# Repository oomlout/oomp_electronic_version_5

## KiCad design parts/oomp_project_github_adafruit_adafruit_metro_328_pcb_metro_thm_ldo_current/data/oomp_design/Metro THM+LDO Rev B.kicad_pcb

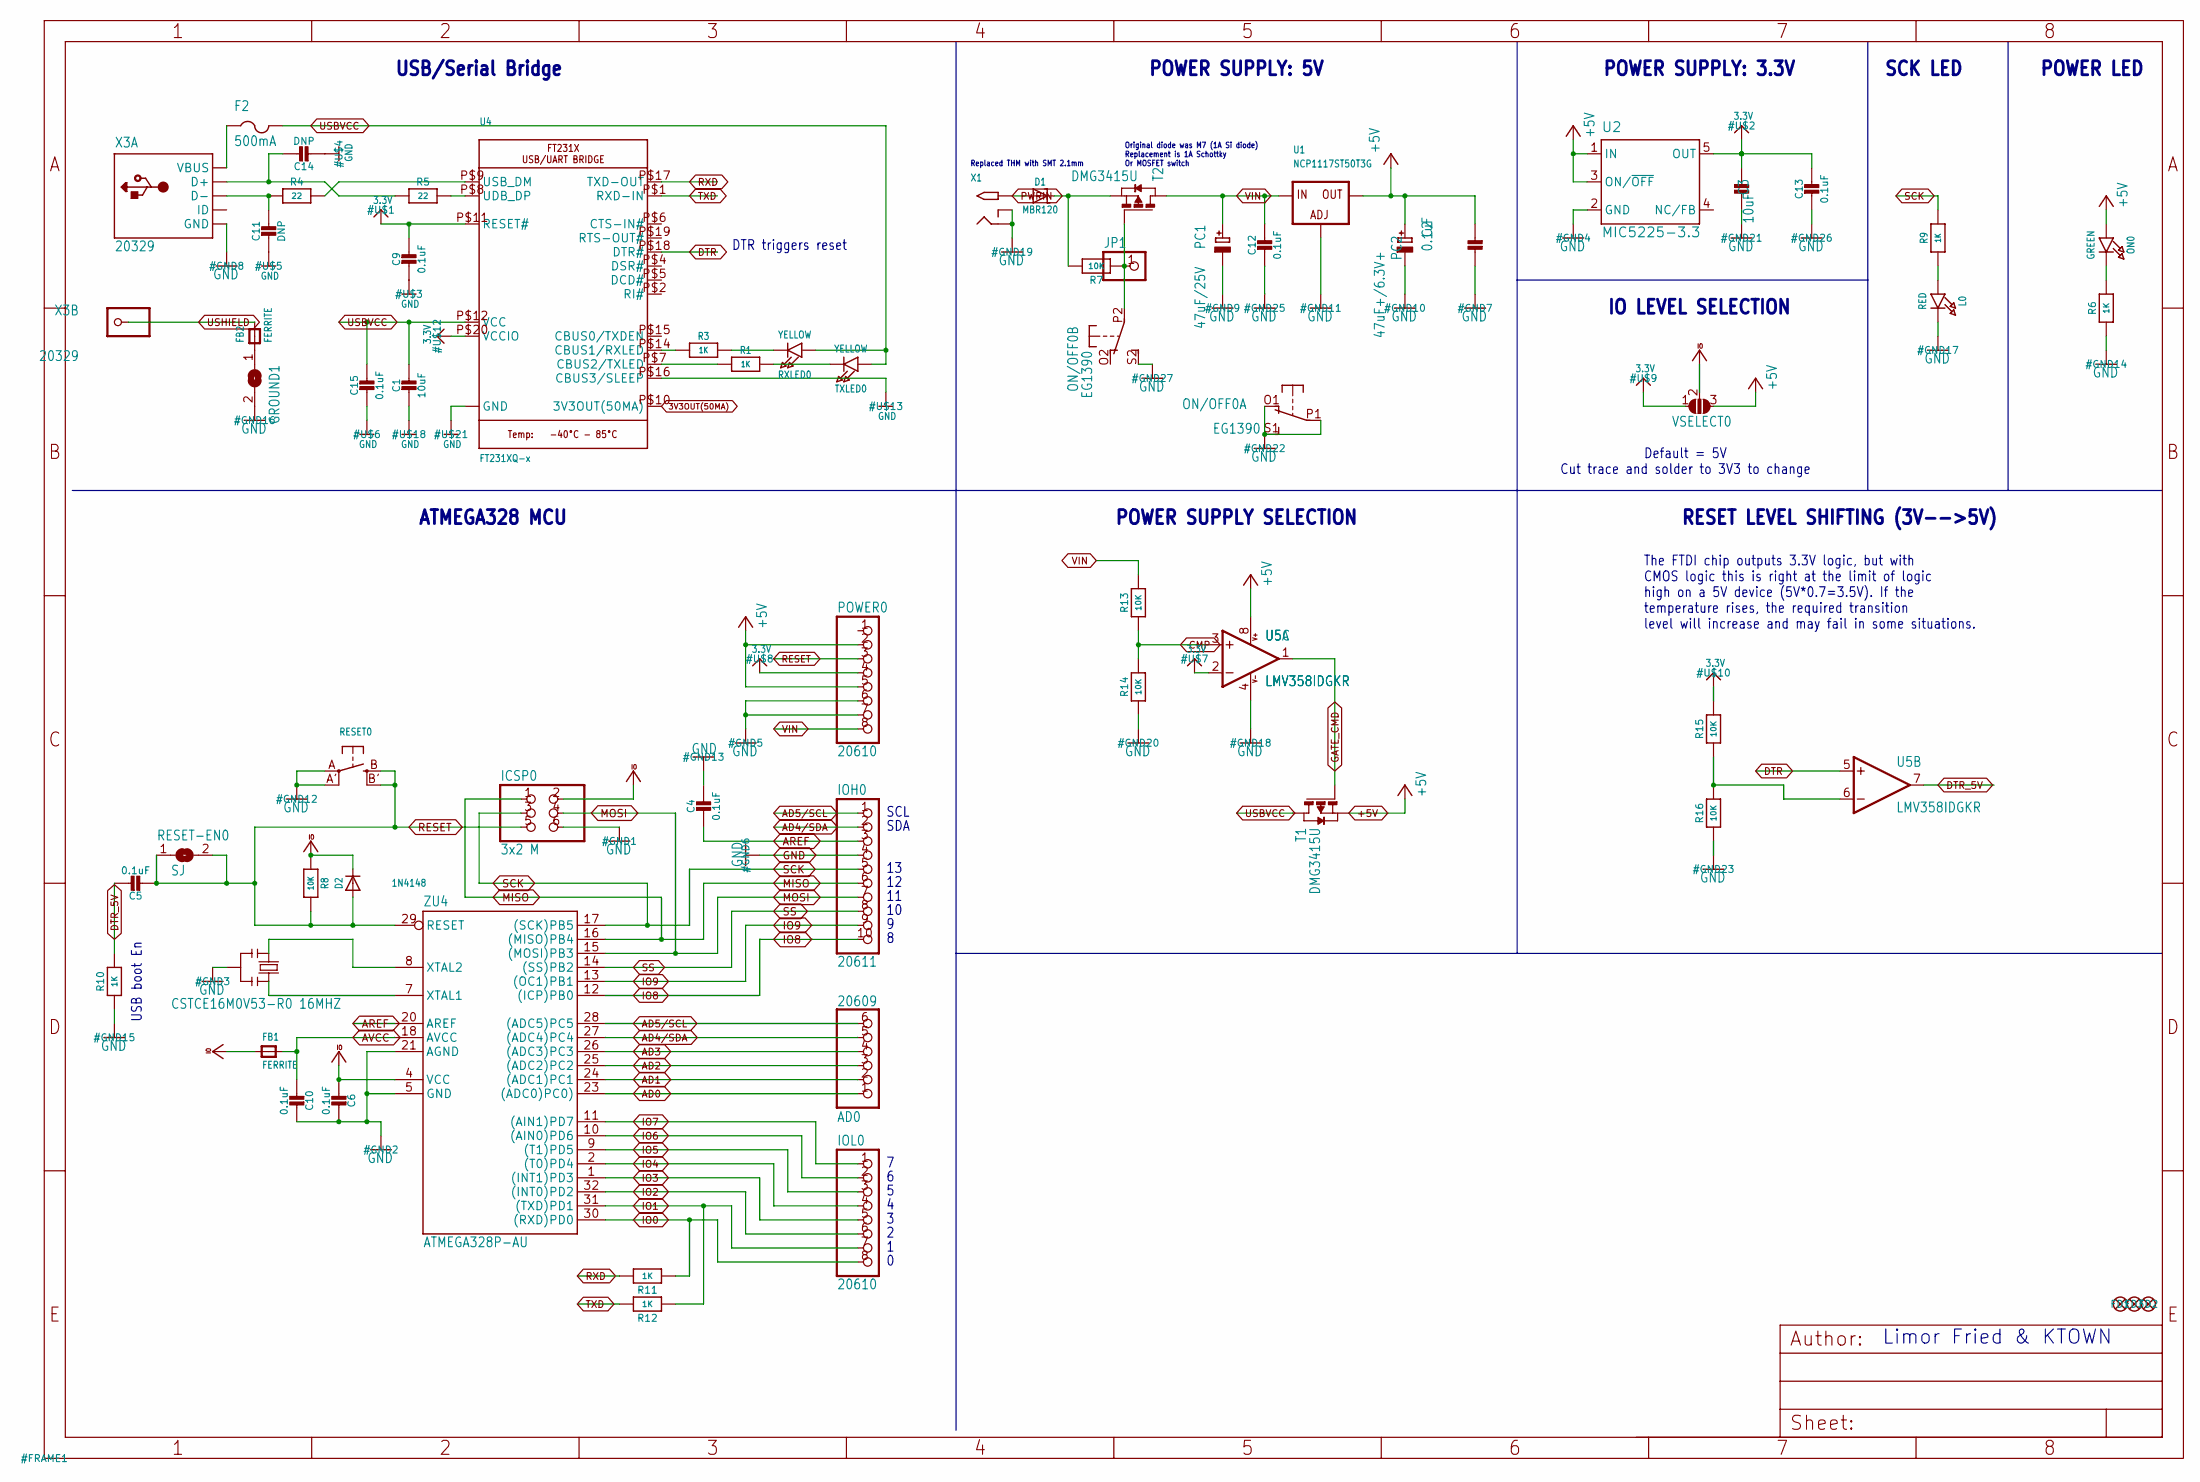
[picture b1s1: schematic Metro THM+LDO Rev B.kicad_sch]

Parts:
AD0: 20609; 1X06_OVAL
C1, C3: 10uF; 0805-NO
C2, C4, C5, C6, C9, C12, C13, C15: 0.1uF; 0805-NO
C10: 0.1uF; 0805_10MGAP
C11, C14: DNP; 0805-NO
D1: MBR120; SOD-123
D2: 1N4148; SOD-323
F2: 500mA; R1206
FB1, FB2: FERRITE; 0805-NO
FD1, FD2, FD3: FIDUCIAL""; FIDUCIAL_1MM
GROUND1: SJ
ICSP0: 3x2 M; 2X03_ROUND_70MIL
IOH0: 20611; 1X10_OVAL
IOL0: 20610; 1X08_OVAL
JP1: HEADER-1X1ROUND; 1X01_ROUND
L0: RED; CHIPLED_0805_NOOUTLINE
ON0: GREEN; CHIPLED_0805_NOOUTLINE
ON/OFF0: EG1390
PC1: 47uF/25V; PANASONIC_D
PC2: 47uF+/6.3V+; PANASONIC_D
POWER0: 20610; 1X08_OVAL
R1, R3, R6, R9, R10, R11, R12: 1K; 0805-NO
R4, R5: 22; 0805-NO
R7, R13, R14, R15, R16: 10K; 0805-NO
R8: 10K; _0805MP
RESET0: SWITCH_TACT_SMT; EVQ-Q2
RESET-EN0: SJ
RXLED0: YELLOW; CHIPLED_0805_NOOUTLINE
T1, T2: DMG3415U; SOT-23
TXLED0: YELLOW; CHIPLED_0805_NOOUTLINE
U1: NCP1117ST50T3G; SOT223-R
U2: MIC5225-3.3; SOT23-DBV
U4: FT231XQ-x; QFN20_4MM
U5: LMV358IDGKR; MSOP08
VSELECT0: SOLDERJUMPER_2WAY; SOLDERJUMPER_2WAY_OPEN_NOPASTE
X1: 2.1MMJACKSMT; DCJACK_2MM_SMT
X3: 20329; 4UCONN_20329
Y2: CSTCE16M0V53-R0 16MHZ; RESONATOR
ZU4: ATMEGA328P-AU; TQFP32-08

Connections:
3.3V: C3.2, C9.1, C13.1, POWER0.4, R15.2, U2.5 (OUT), U4.P$11 (RESET#), U4.P$20 (VCCIO), U5.2 (-IN), VSELECT0.1
3V3OUT(50MA): U4.P$10 (3V3OUT(50MA))
+5V: C2.2, ON0.A, PC2.+, POWER0.2, POWER0.5, T1.2 (S), U1.2 (OUT), U1.4 (OUT), U2.1 (IN), U2.3 (ON/~OFF), U5.8 (V+), VSELECT0.3
AD0: AD0.1, ZU4.23 ((ADC0)PC0))
AD1: AD0.2, ZU4.24 ((ADC1)PC1)
AD2: AD0.3, ZU4.25 ((ADC2)PC2)
AD3: AD0.4, ZU4.26 ((ADC3)PC3)
AD4/SDA: AD0.5, IOH0.2, ZU4.27 ((ADC4)PC4)
AD5/SCL: AD0.6, IOH0.1, ZU4.28 ((ADC5)PC5)
AREF: C4.2, IOH0.3, ZU4.20 (AREF)
AVCC: C10.2, FB1.2, ZU4.18 (AVCC)
CMP: R13.1, R14.2, U5.3 (+IN)
D+: C14.1, R5.1, X3.D+
D-: C11.1, R4.1, X3.D-
DTR: U4.P$18 (DTR#), U5.5 (+IN)
DTR_5V: C5.1, R10.2, U5.7 (OUT)
GATE_CMD: T1.3 (G), U5.1 (OUT)
GND: C1.2, C2.1, C3.1, C4.1, C6.1, C9.2, C10.1, C11.2, C12.2, C13.2, C14.2, C15.2, GROUND1.2, ICSP0.6, IOH0.4, L0.C, ON/OFF0.O1 (O), ON/OFF0.P1, ON/OFF0.S1 (S), ON/OFF0.S2 (S), PC1.-, PC2.-, POWER0.6, POWER0.7, R6.1, R10.1, R14.1, R16.1, RESET0.A, RESET0.A' (P1), U1.1 (ADJ), U2.2 (GND), U4.P$3 (GND), U4.P$13 (GND), U4.P$16 (CBUS3/SLEEP), U4.P$21 (GND), U5.4 (V-), X1.GND (RING), X1.GNDBREAK (RING_SW), X3.GND, Y2.2, ZU4.5 (GND), ZU4.21 (AGND)
IO0: IOL0.8, R11.1, ZU4.30 ((RXD)PD0)
IO1: IOL0.7, R12.1, ZU4.31 ((TXD)PD1)
IO2: IOL0.6, ZU4.32 ((INT0)PD2)
IO3: IOL0.5, ZU4.1 ((INT1)PD3)
IO4: IOL0.4, ZU4.2 ((T0)PD4)
IO5: IOL0.3, ZU4.9 ((T1)PD5)
IO6: IOL0.2, ZU4.10 ((AIN0)PD6)
IO7: IOL0.1, ZU4.11 ((AIN1)PD7)
IO8: IOH0.10, ZU4.12 ((ICP)PB0)
IO9: IOH0.9, ZU4.13 ((OC1)PB1)
MISO: ICSP0.1, IOH0.6, ZU4.16 ((MISO)PB4)
MOSI: ICSP0.4, IOH0.7, ZU4.15 ((MOSI)PB3)
unnamed: L0.A, R9.1
unnamed: FB2.1, GROUND1.1
unnamed: ON0.C, R6.2
unnamed: R3.2, U4.P$14 (CBUS1/RXLED)
unnamed: R3.1, RXLED0.C
unnamed: R1.2, U4.P$7 (CBUS2/TXLED)
unnamed: R1.1, TXLED0.C
unnamed: R4.2, U4.P$9 (USB_DM)
unnamed: R5.2, U4.P$8 (UDB_DP)
unnamed: R15.1, R16.2, U5.6 (-IN)
unnamed: JP1.1, ON/OFF0.P2, R7.1, T2.3 (G)
unnamed: D1.C, R7.2, T2.2 (S)
PWRIN: D1.A, X1.PWR2 (TIP)
RESET: C5.2, D2.A, ICSP0.5, POWER0.3, R8.1, RESET0.B (S), RESET0.B' (S1), RESET-EN0.1, RESET-EN0.2, ZU4.29 (RESET)
RXD: R11.2, U4.P$17 (TXD-OUT)
SCK: ICSP0.3, IOH0.5, R9.2, ZU4.17 ((SCK)PB5)
SS: IOH0.8, ZU4.14 ((SS)PB2)
TXD: R12.2, U4.P$1 (RXD-IN)
USBVCC: C1.1, C15.1, F2.2, RXLED0.A, T1.1 (D), TXLED0.A, U4.P$12 (VCC)
USHIELD: FB2.2, X3.BASE@1 (1), X3.BASE@2 (1), X3.SPRT@1 (1), X3.SPRT@2 (1), X3.SPRT@3 (1), X3.SPRT@4 (1)
VBUS: F2.1, X3.VBUS
VCCIO: C6.2, D2.C, FB1.1, ICSP0.2, R8.2, VSELECT0.2, ZU4.4 (VCC)
VIN: C12.1, PC1.+, POWER0.8, R13.2, T2.1 (D), U1.3 (IN)
XTAL1: Y2.3, ZU4.7 (XTAL1)
XTAL2: Y2.1, ZU4.8 (XTAL2)

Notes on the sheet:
Limor Fried & KTOWN
SDA
POWER SUPPLY SELECTION
Original diode was M7 (1A Si diode) Replacement is 1A Schottky Or MOSFET switch
POWER SUPPLY: 3.3V
POWER LED
The FTDI chip outputs 3.3V logic, but with CMOS logic this is right at the limit of logic high on a 5V device (5V*0.7=3.5V). If the temperature rises, the required transition level will increase and may fail in some situations.
Default = 5V Cut trace and solder to 3V3 to change
SCK LED
RESET LEVEL SHIFTING (3V-->5V)
SCL
USB boot En
IO LEVEL SELECTION
DTR triggers reset
USB/Serial Bridge
POWER SUPPLY: 5V
Replaced THM with SMT 2.1mm
ATMEGA328 MCU

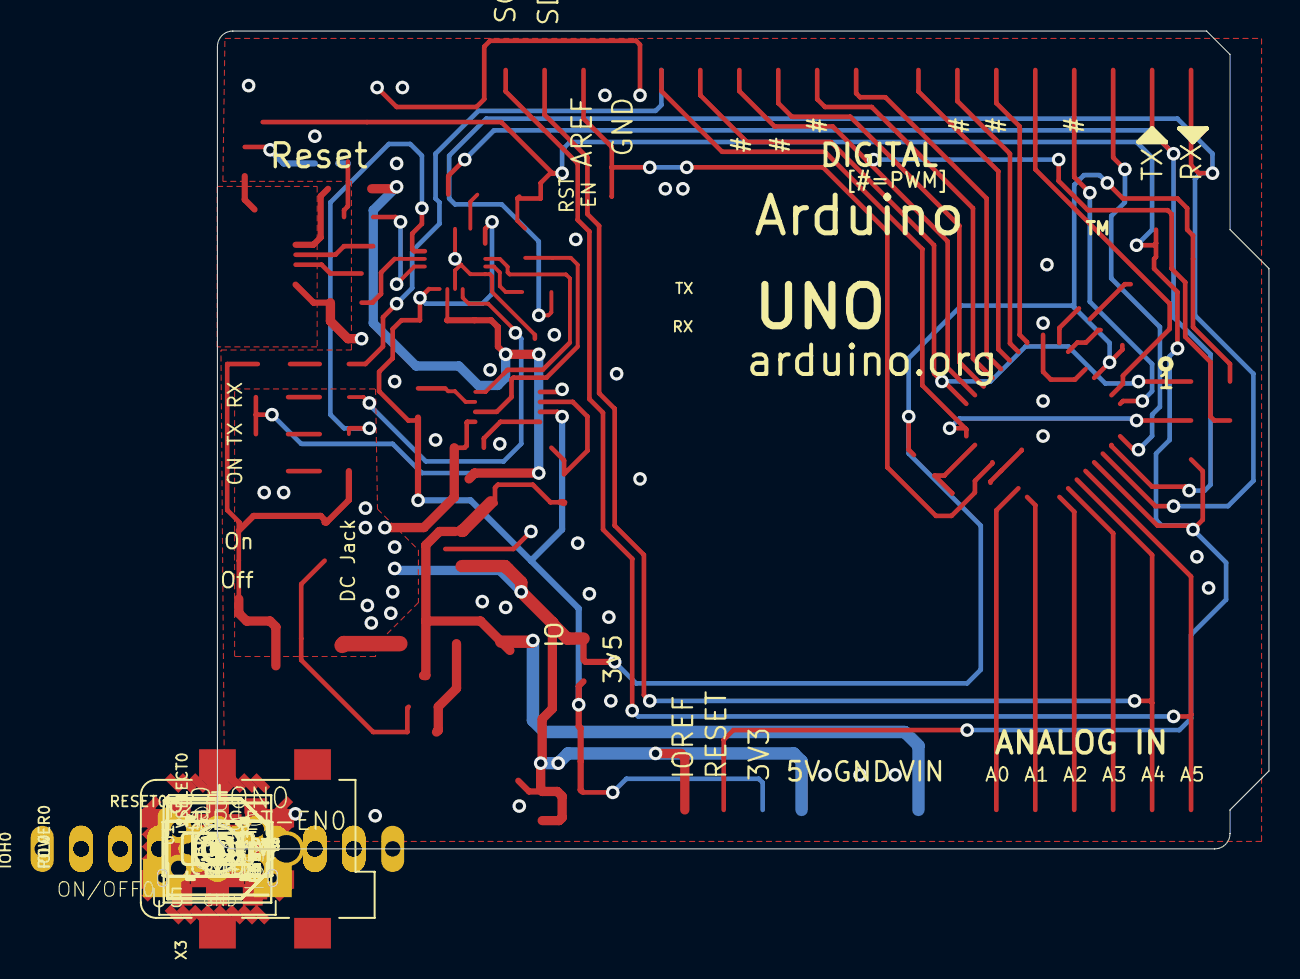
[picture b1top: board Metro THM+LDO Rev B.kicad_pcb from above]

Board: 2 copper layers, 72.5 x 55.8 mm, 70 parts (1 on the bottom side), 54 nets.

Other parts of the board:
U$11: METROSILK_TOP
U$14: METROSILK_BOT
U$15: PCBFEAT-REV-040
UNK_HOLE_0: dummyfp0
UNK_HOLE_1: dummyfp1
UNK_HOLE_2: dummyfp2
UNK_HOLE_3: dummyfp3

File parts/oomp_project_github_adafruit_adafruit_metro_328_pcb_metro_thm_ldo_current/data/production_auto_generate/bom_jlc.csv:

Comment,Designator,Footprint,LCSC Part #
,JP1,Metro THM+LDO Rev B-import-fps:1X01_ROUND,C7501259
,RESET0,Metro THM+LDO Rev B-import-fps:EVQ-Q2,
,U$14,Metro THM+LDO Rev B-import-fps:METROSILK_BOT,
,U$11,Metro THM+LDO Rev B-import-fps:METROSILK_TOP,
,U$15,Metro THM+LDO Rev B-import-fps:PCBFEAT-REV-040,
,"GROUND1,RESET-EN0",Metro THM+LDO Rev B-import-fps:SJ,
,VSELECT0,Metro THM+LDO Rev B-import-fps:SOLDERJUMPER_2WAY_OPEN_NOPASTE,
0.1uF,"C2,C4,C5,C6,C9,C12,C13,C15",Metro THM+LDO Rev B-import-fps:0805-NO,
0.1uF,C10,Metro THM+LDO Rev B-import-fps:0805_10MGAP,
10K,"R7,R13,R14,R15,R16",Metro THM+LDO Rev B-import-fps:0805-NO,C17414
10K,R8,Metro THM+LDO Rev B-import-fps:_0805MP,C17414
10uF,"C1,C3",Metro THM+LDO Rev B-import-fps:0805-NO,
1K,"R1,R3,R6,R9,R10,R11,R12",Metro THM+LDO Rev B-import-fps:0805-NO,C17513
1N4148,D2,Metro THM+LDO Rev B-import-fps:SOD-323,
2.1MMJACKSMT,X1,Metro THM+LDO Rev B-import-fps:DCJACK_2MM_SMT,
20329,X3,Metro THM+LDO Rev B-import-fps:4UCONN_20329,
20609,AD0,Metro THM+LDO Rev B-import-fps:1X06_OVAL,C37208
20610,"IOL0,POWER0",Metro THM+LDO Rev B-import-fps:1X08_OVAL,C492421
20611,IOH0,Metro THM+LDO Rev B-import-fps:1X10_OVAL,C57369
22,"R4,R5",Metro THM+LDO Rev B-import-fps:0805-NO,C2907310
3x2 M,ICSP0,Metro THM+LDO Rev B-import-fps:2X03_ROUND_70MIL,
47uF+/6.3V+,PC2,Metro THM+LDO Rev B-import-fps:PANASONIC_D,
47uF/25V,PC1,Metro THM+LDO Rev B-import-fps:PANASONIC_D,
500mA,F2,Metro THM+LDO Rev B-import-fps:R1206,
ATMEGA328P-AU,ZU4,Metro THM+LDO Rev B-import-fps:TQFP32-08,
CSTCE16M0V53-R0 16MHZ,Y2,Metro THM+LDO Rev B-import-fps:RESONATOR,
DMG3415U,"T1,T2",Metro THM+LDO Rev B-import-fps:SOT-23,
DNP,"C11,C14",Metro THM+LDO Rev B-import-fps:0805-NO,
EG1390,ON/OFF0,Metro THM+LDO Rev B-import-fps:EG1390,
FERRITE,"FB1,FB2",Metro THM+LDO Rev B-import-fps:0805-NO,
"FIDUCIAL""""","FD1,FD2,FD3",Metro THM+LDO Rev B-import-fps:FIDUCIAL_1MM,
FT231XQ-x ,U4,Metro THM+LDO Rev B-import-fps:QFN20_4MM,
GREEN,ON0,Metro THM+LDO Rev B-import-fps:CHIPLED_0805_NOOUTLINE,
LMV358IDGKR,U5,Metro THM+LDO Rev B-import-fps:MSOP08,
MBR120,D1,Metro THM+LDO Rev B-import-fps:SOD-123,
MIC5225-3.3,U2,Metro THM+LDO Rev B-import-fps:SOT23-DBV,
NCP1117ST50T3G,U1,Metro THM+LDO Rev B-import-fps:SOT223-R,
RED,L0,Metro THM+LDO Rev B-import-fps:CHIPLED_0805_NOOUTLINE,
YELLOW,"RXLED0,TXLED0",Metro THM+LDO Rev B-import-fps:CHIPLED_0805_NOOUTLINE,

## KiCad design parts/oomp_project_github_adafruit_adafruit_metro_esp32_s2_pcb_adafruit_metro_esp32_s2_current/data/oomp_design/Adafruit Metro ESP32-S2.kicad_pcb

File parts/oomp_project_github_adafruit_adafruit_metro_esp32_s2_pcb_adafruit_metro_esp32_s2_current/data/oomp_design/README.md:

# OOMP KiCad design copy

Open `Adafruit Metro ESP32-S2.kicad_pro` (or the `.kicad_pcb` / `.kicad_sch`) in KiCad. Local OOMP libraries are under `libraries/`. Original inputs are preserved in [../original/](../original/).

Only verified unchanged installed KiCad defaults were renamed. Modified, custom, unmatched and unavailable items remain unchanged. Soldering variants are never swapped during conversion. Existing pad coordinates, nets and UUIDs are preserved.

See [conversion_report.yaml](conversion_report.yaml) for every conversion and skip. Copy this directory before editing; regeneration refuses to overwrite edited design files.

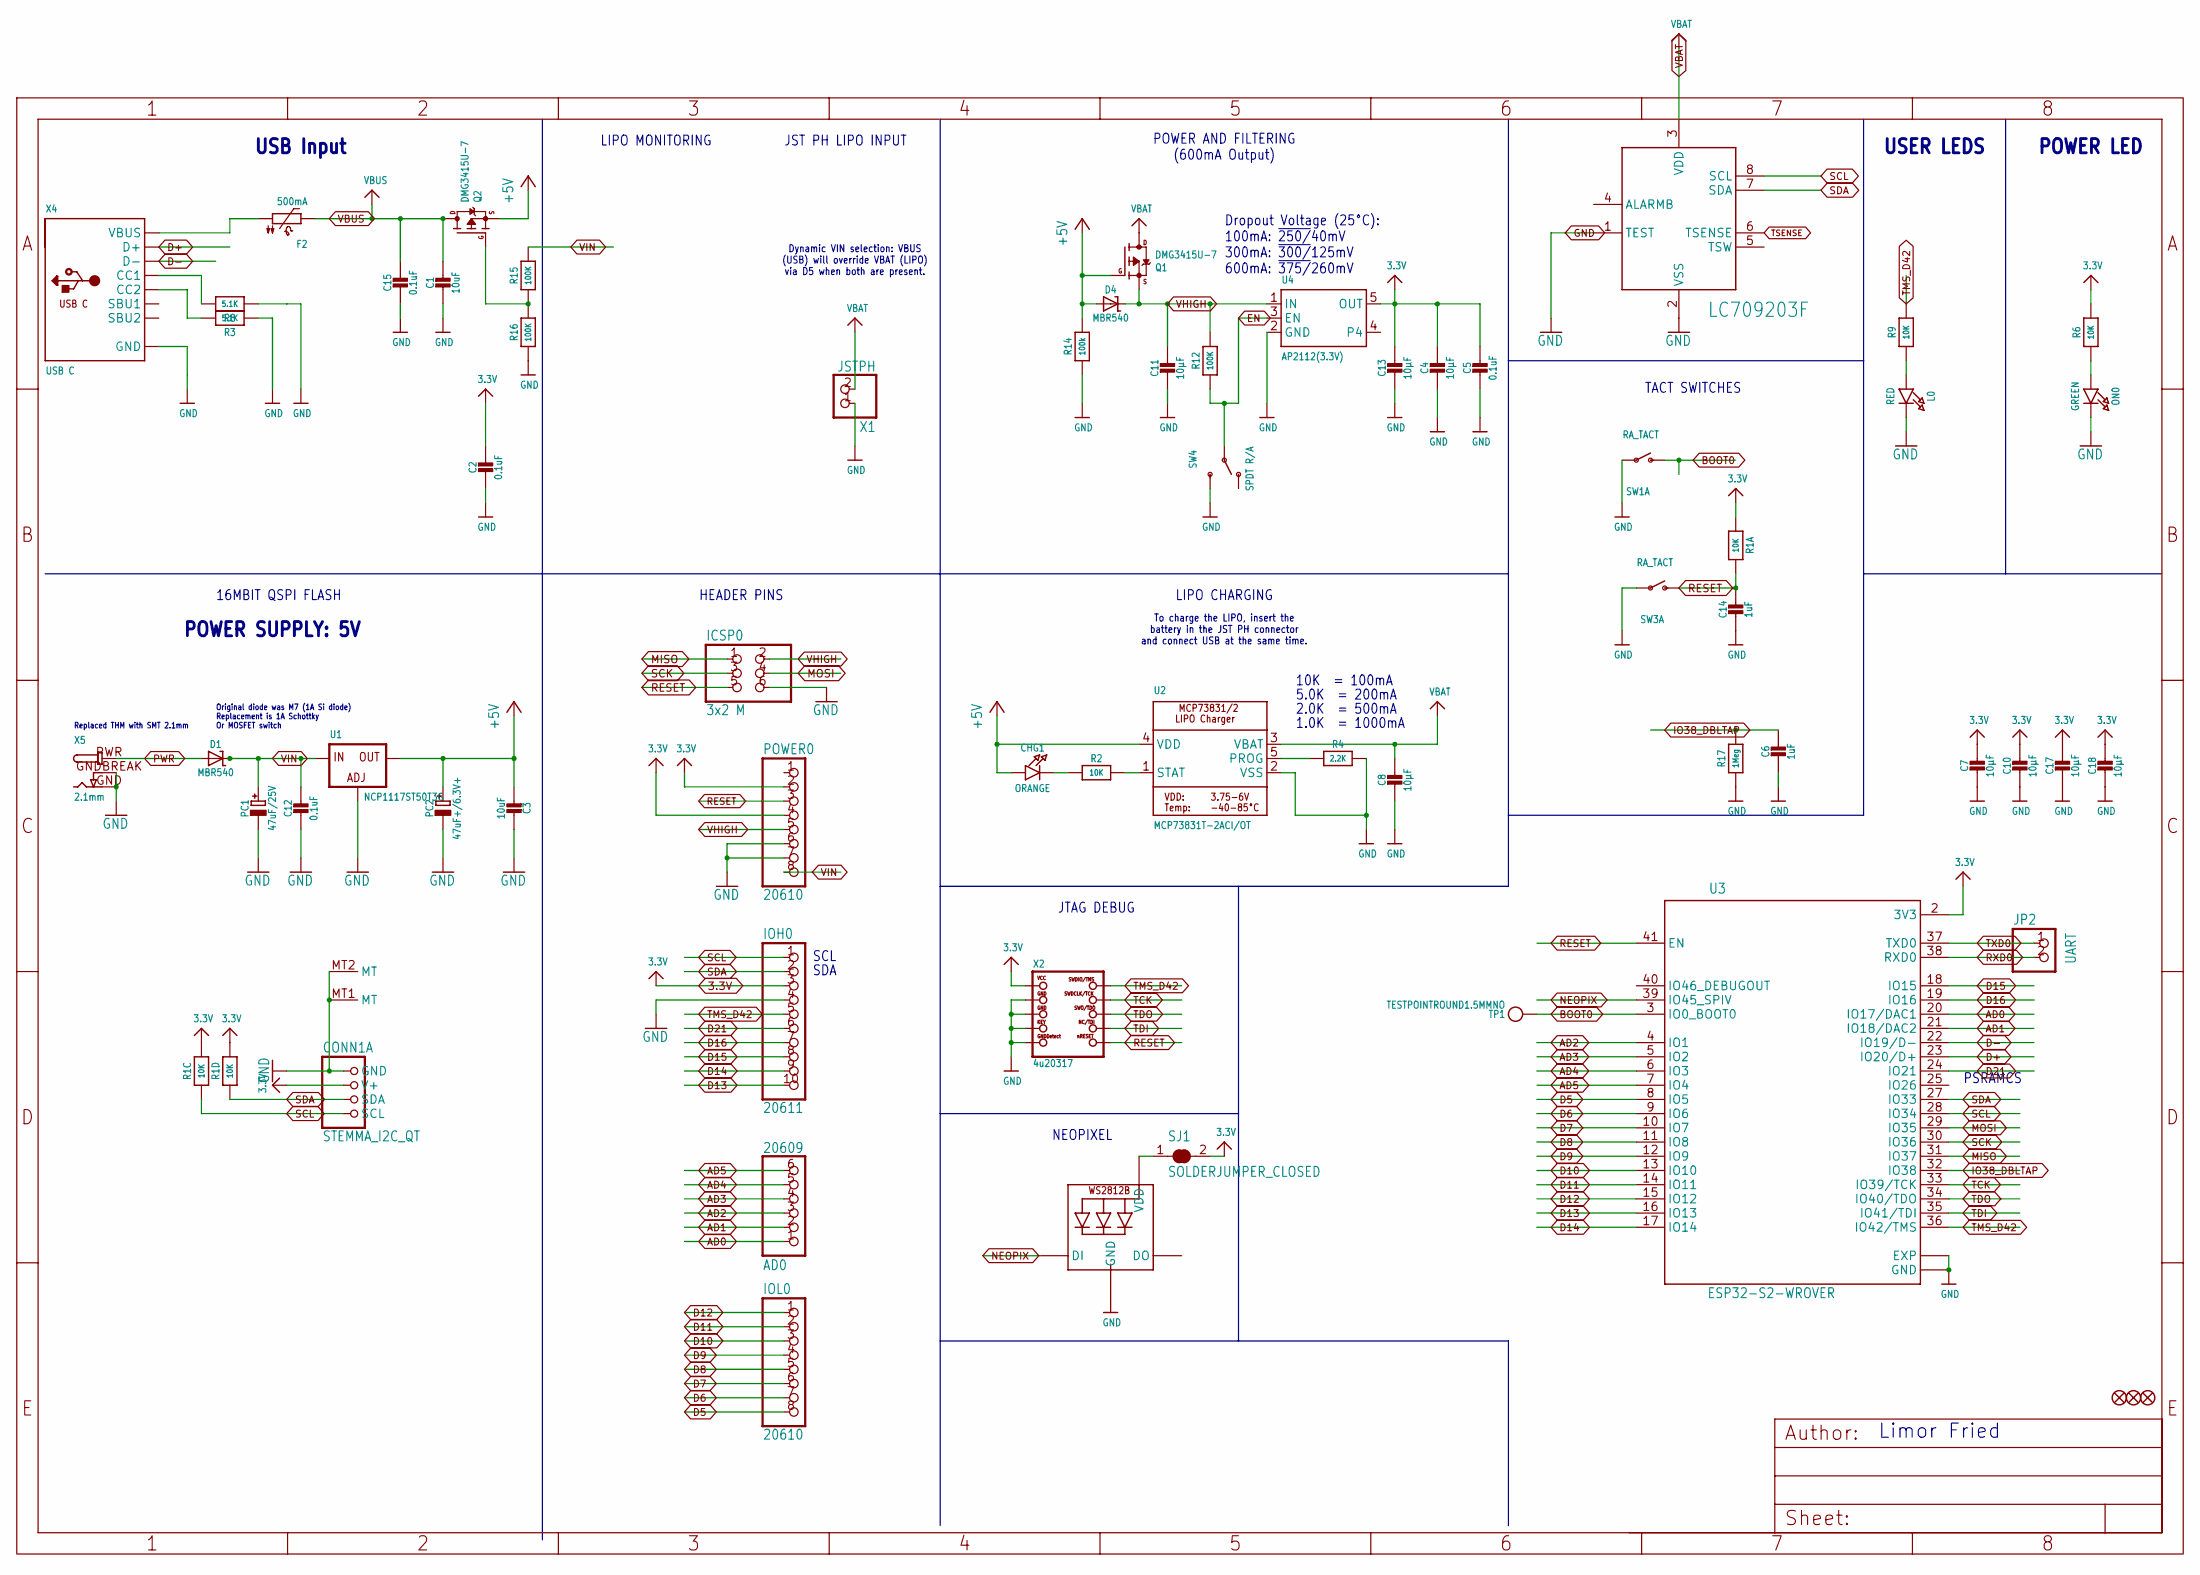
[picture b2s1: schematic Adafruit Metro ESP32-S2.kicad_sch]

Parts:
AD0: 20609; 1X06_OVALWAVE
C1, C3: 10uF; 0805-NO
C2, C5, C12, C15: 0.1uF; 0603-NO
C4, C7, C8, C10, C11, C13, C17, C18: 10µF; 0805-NO
C6, C14: 1uF; 0603-NO
CHG1: ORANGE; CHIPLED_0603_NOOUTLINE
CONN1: STEMMA_I2C_QT; JST_SH4
D1, D4: MBR540; SOD-123
F2: 500mA; 1206
FD1, FD2, FD3: FIDUCIAL_1MM
IC2: LC709203F; WDFN8_3X4_0.65
ICSP0: 3x2 M; 2X03_ROUND_70MIL
IOH0: 20611; 1X10_OVALWAVE
IOL0: 20610; 1X08_OVALWAVE
JP2: UART; 1X02_ROUND
L0: RED; CHIPLED_0603_NOOUTLINE
LED1: WS2812B3535; LED3535
ON0: GREEN; CHIPLED_0603_NOOUTLINE
PC1: 47uF/25V; PANASONIC_D
PC2: 47uF+/6.3V+; PANASONIC_D
POWER0: 20610; 1X08_OVALWAVE
Q1, Q2: DMG3415U-7; SOT23-R
R1: 10K; RESPACK_4X0603
R2, R6, R9: 10K; 0603-NO
R3, R8: 5.1K; 0603-NO
R4: 2.2K; 0603-NO
R12, R15, R16: 100K; 0603-NO
R14: 100k; 0603-NO
R17: 1Meg; 0603-NO
SJ1: SOLDERJUMPER_CLOSED; SOLDERJUMPER_CLOSEDWIRE
SW1, SW3: RA_TACT; SPST_TACTILE_RA
SW4: SPDT R/A; SPDT_SMT_SSSS811101
TP1: TESTPOINTROUND1.5MMNO; TESTPOINT_ROUND_1.5MM_NO
U1: NCP1117ST50T3G; SOT223-R
U2: MCP73831T-2ACI/OT; SOT23-5
U3: ESP32-S2-WROVER; MODULE_ESP32-S2-WROVER
U4: AP2112(3.3V); SOT23-5
X1: JSTPH; JSTPH2_BATT
X2: 4u20317; 2X05_1.27MM_BOX_POSTS
X4: USB C; USB_C_CUSB31-CFM2AX-01-X
X5: 2.1mm; DCJACK_2MM_PTH

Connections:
3.3V: C2.1, C4.1, C5.1, C7.1, C10.1, C13.1, C17.1, C18.1, CONN1.2 (V+), IOH0.3, POWER0.2, POWER0.4, R1.1, R1.5 (2), R1.6 (2), R6.2, SJ1.2, U3.2 (3V3), U4.5 (OUT), X2.1 (VCC)
+5V: C3.2, CHG1.A, D4.A, PC2.+, Q1.1 (G), Q2.2 (S), R14.2, U1.2 (OUT), U1.4 (OUT), U2.4 (VDD)
AD0: AD0.1, U3.20 (IO17/DAC1)
AD1: AD0.2, U3.21 (IO18/DAC2)
AD2: AD0.3, U3.4 (IO1)
AD3: AD0.4, U3.5 (IO2)
AD4: AD0.5, U3.6 (IO3)
AD5: AD0.6, U3.7 (IO4)
BOOT0: SW1.2 (S), TP1.P$1, U3.3 (IO0_BOOT0)
D5: IOL0.8, U3.8 (IO5)
D6: IOL0.7, U3.9 (IO6)
D7: IOL0.6, U3.10 (IO7)
D8: IOL0.5, U3.11 (IO8)
D9: IOL0.4, U3.12 (IO9)
D10: IOL0.3, U3.13 (IO10)
D11: IOL0.2, U3.14 (IO11)
D12: IOL0.1, U3.15 (IO12)
D13: IOH0.10, U3.16 (IO13)
D14: IOH0.9, U3.17 (IO14)
D15: IOH0.8, U3.18 (IO15)
D16: IOH0.7, U3.19 (IO16)
D21: IOH0.6, U3.24 (IO21)
D+: U3.23 (IO20/D+), X4.A6 (D+), X4.B6 (D+)
D-: U3.22 (IO19/D-), X4.A7 (D-), X4.B7 (D-)
EN: R12.1, SW4.B, U4.3 (EN)
GND: C1.2, C2.2, C3.1, C4.2, C5.2, C6.2, C7.2, C8.2, C10.2, C11.2, C12.2, C13.2, C14.2, C15.2, C17.2, C18.2, CONN1.1 (GND), CONN1.MT1 (MT), CONN1.MT2 (MT), IC2.1 (TEST), IC2.2 (VSS), ICSP0.6, IOH0.4, L0.C, LED1.4 (GND), ON0.C, PC1.-, PC2.-, POWER0.6, POWER0.7, R3.1, R4.2, R8.1, R14.1, R16.1, R17.1, SW1.1, SW3.1, SW4.C (S), U1.1 (ADJ), U2.2 (VSS), U3.1 (GND), U3.26 (GND), U3.42 (GND), U3.43_1 (EXP), U3.43_2 (EXP), U3.43_3 (EXP), U3.43_4 (EXP), U3.43_5 (EXP), U3.43_6 (EXP), U3.43_7 (EXP), U3.43_8 (EXP), U3.43_9 (EXP), U3.43_10 (EXP), U3.43_11 (EXP), U3.43_12 (EXP), U3.43_13 (EXP), U3.43_14 (EXP), U3.43_15 (EXP), U3.43_16 (EXP), U3.43_17 (EXP), U3.43_18 (EXP), U3.43_19 (EXP), U3.43_20 (EXP), U3.43_21 (EXP), U4.2 (GND), X1.1, X2.3 (GND), X2.5 (GND), X2.7 (KEY), X2.9 (GNDDETECT), X4.A1B12 (GND), X4.B1A12 (GND), X5.GND, X5.GNDBREAK
IO38_DBLTAP: C6.1, R17.2, U3.32 (IO38)
MISO: ICSP0.1, U3.31 (IO37)
MOSI: ICSP0.4, U3.29 (IO35)
unnamed: L0.A, R9.1
unnamed: Q2.1 (G), R15.1, R16.2
unnamed: ON0.A, R6.1
unnamed: CHG1.C, R2.1
unnamed: LED1.2 (VDD), SJ1.1
unnamed: R2.2, U2.1 (STAT)
unnamed: R8.2, X4.A5 (CC1)
unnamed: R3.2, X4.B5 (CC2)
unnamed: R4.1, U2.5 (PROG)
unnamed: F2.1, X4.A4B9 (VBUS), X4.B4A9 (VBUS)
NEOPIX: LED1.1 (DI), U3.39 (IO45_SPIV)
PWR: D1.A, X5.PWR
RESET: C14.1, ICSP0.5, POWER0.3, R1.8 (2), SW3.2 (S), U3.41 (EN), X2.10 (NRESET)
RXD0: JP2.2, U3.38 (RXD0)
SCK: ICSP0.3, U3.30 (IO36)
SCL: CONN1.4 (SCL), IC2.8 (SCL), IOH0.1, R1.3 (1), U3.28 (IO34)
SDA: CONN1.3 (SDA), IC2.7 (SDA), IOH0.2, R1.4 (1), U3.27 (IO33)
TCK: U3.33 (IO39/TCK), X2.4 (SWDCLK)
TDI: U3.35 (IO41/TDI), X2.8 (TDI)
TDO: U3.34 (IO40/TDO), X2.6 (SWO)
TMS_D42: IOH0.5, R9.2, U3.36 (IO42/TMS), X2.2 (SWDIO)
TXD0: JP2.1, U3.37 (TXD0)
VBAT: C8.1, IC2.3 (VDD), Q1.3 (D), U2.3 (VBAT), X1.2
VBUS: C1.1, C15.1, F2.2, Q2.3 (D)
VHIGH: C11.1, D4.C, ICSP0.2, POWER0.5, Q1.2 (S), R12.2, U4.1 (IN)
VIN: C12.1, D1.C, PC1.+, POWER0.8, R15.2, U1.3 (IN)

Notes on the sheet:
16MBIT QSPI FLASH
POWER AND FILTERING (600mA Output)
PSRAMCS
POWER LED
Original diode was M7 (1A Si diode) Replacement is 1A Schottky Or MOSFET switch
JST PH LIPO INPUT
1.0K = 1000mA
Limor Fried
SDA
NEOPIXEL
To charge the LIPO, insert the battery in the JST PH connector and connect USB at the same time.
LIPO MONITORING
SCL
USB Input
Replaced THM with SMT 2.1mm
Dropout Voltage (25°C): 100mA: ~{250/}40mV 300mA: ~{300/}125mV 600mA: ~{375/}260mV
POWER SUPPLY: 5V
JTAG DEBUG
10K = 100mA
HEADER PINS
2.0K = 500mA
Dynamic VIN selection: VBUS (USB) will override VBAT (LIPO) via D5 when both are present.
5.0K = 200mA
TACT SWITCHES
USER LEDS
LIPO CHARGING

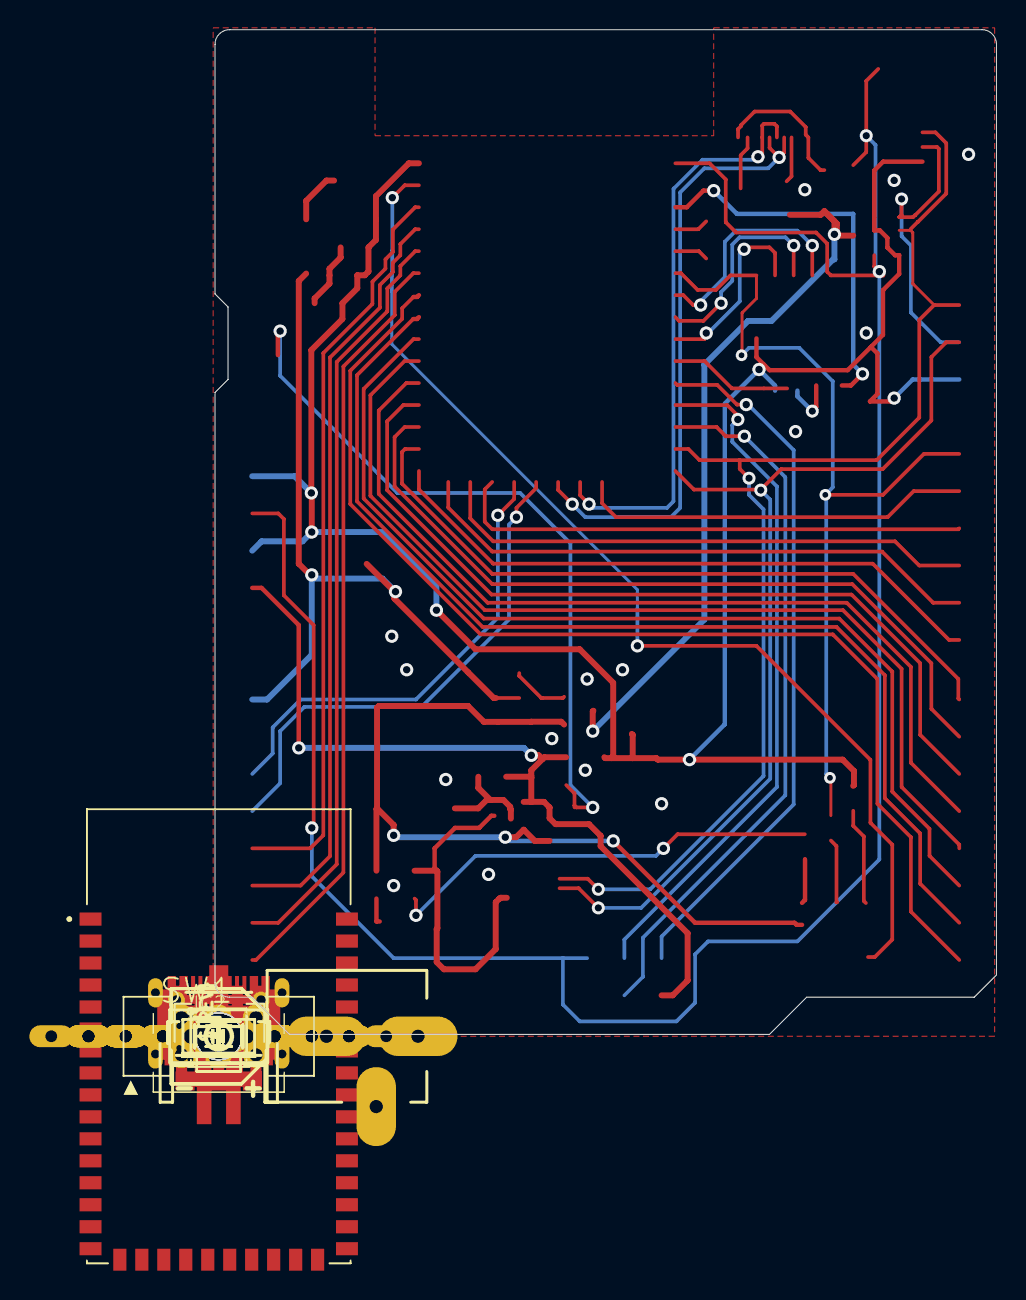
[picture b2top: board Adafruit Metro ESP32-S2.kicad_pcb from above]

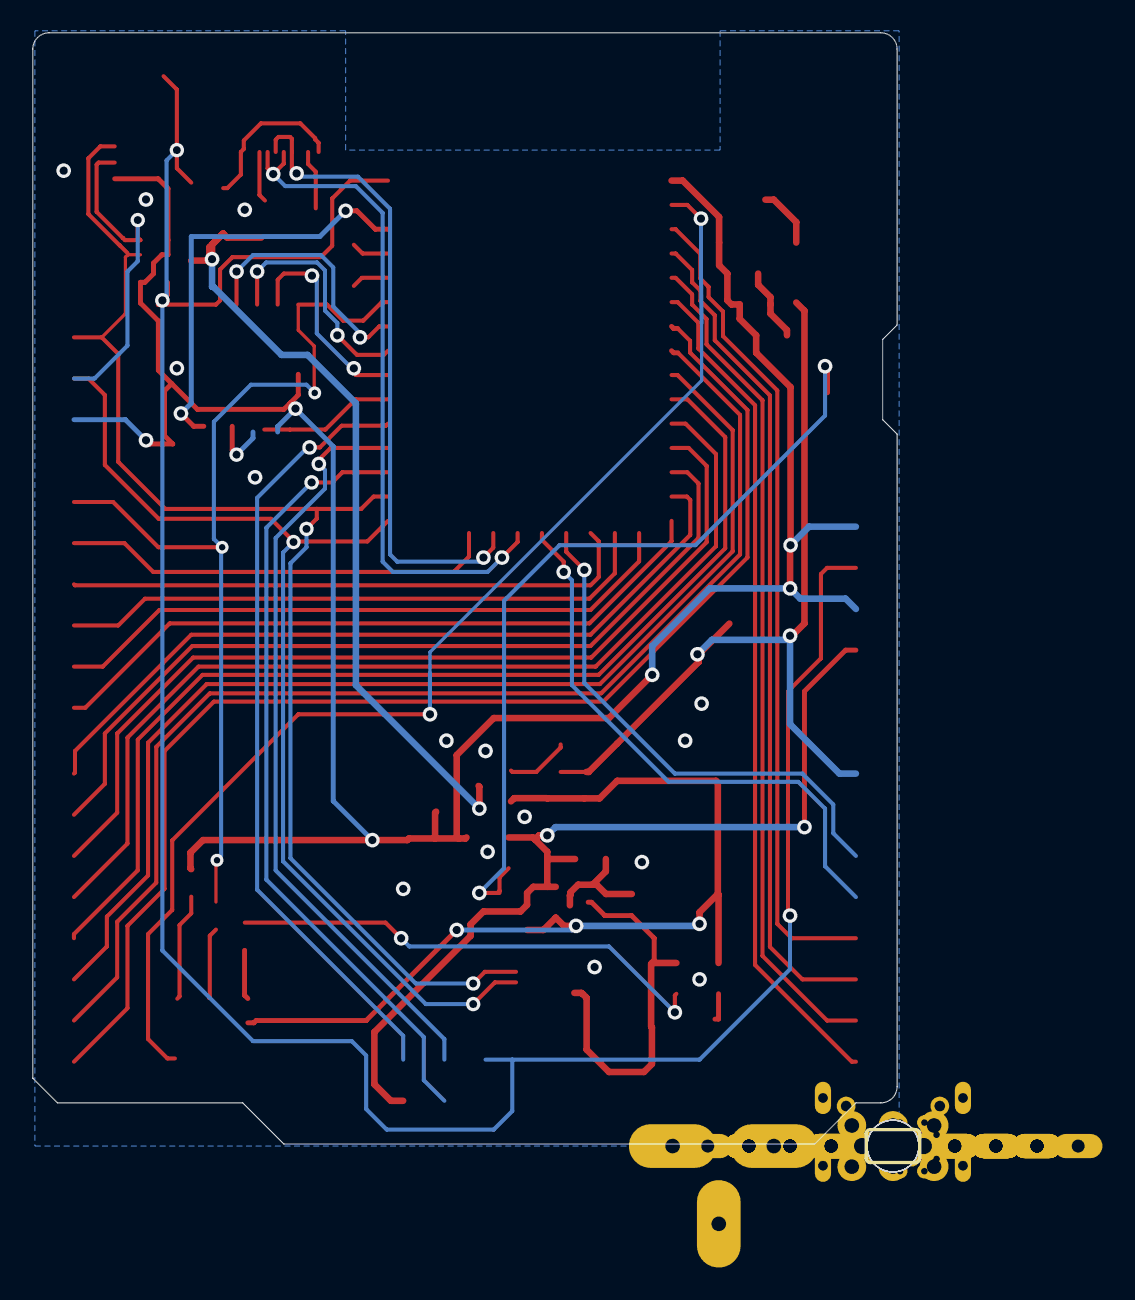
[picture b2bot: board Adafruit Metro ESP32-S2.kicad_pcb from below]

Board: 2 copper layers, 53.3 x 68.6 mm, 70 parts (3 on the bottom side), 55 nets.

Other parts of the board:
U$15: PCBFEAT-REV-040
U$52: ESP32S2_TOP
U$53: ESP32S2_BOT
UNK_HOLE_0: dummyfp0
UNK_HOLE_1: dummyfp1
UNK_HOLE_2: dummyfp2
UNK_HOLE_3: dummyfp3
